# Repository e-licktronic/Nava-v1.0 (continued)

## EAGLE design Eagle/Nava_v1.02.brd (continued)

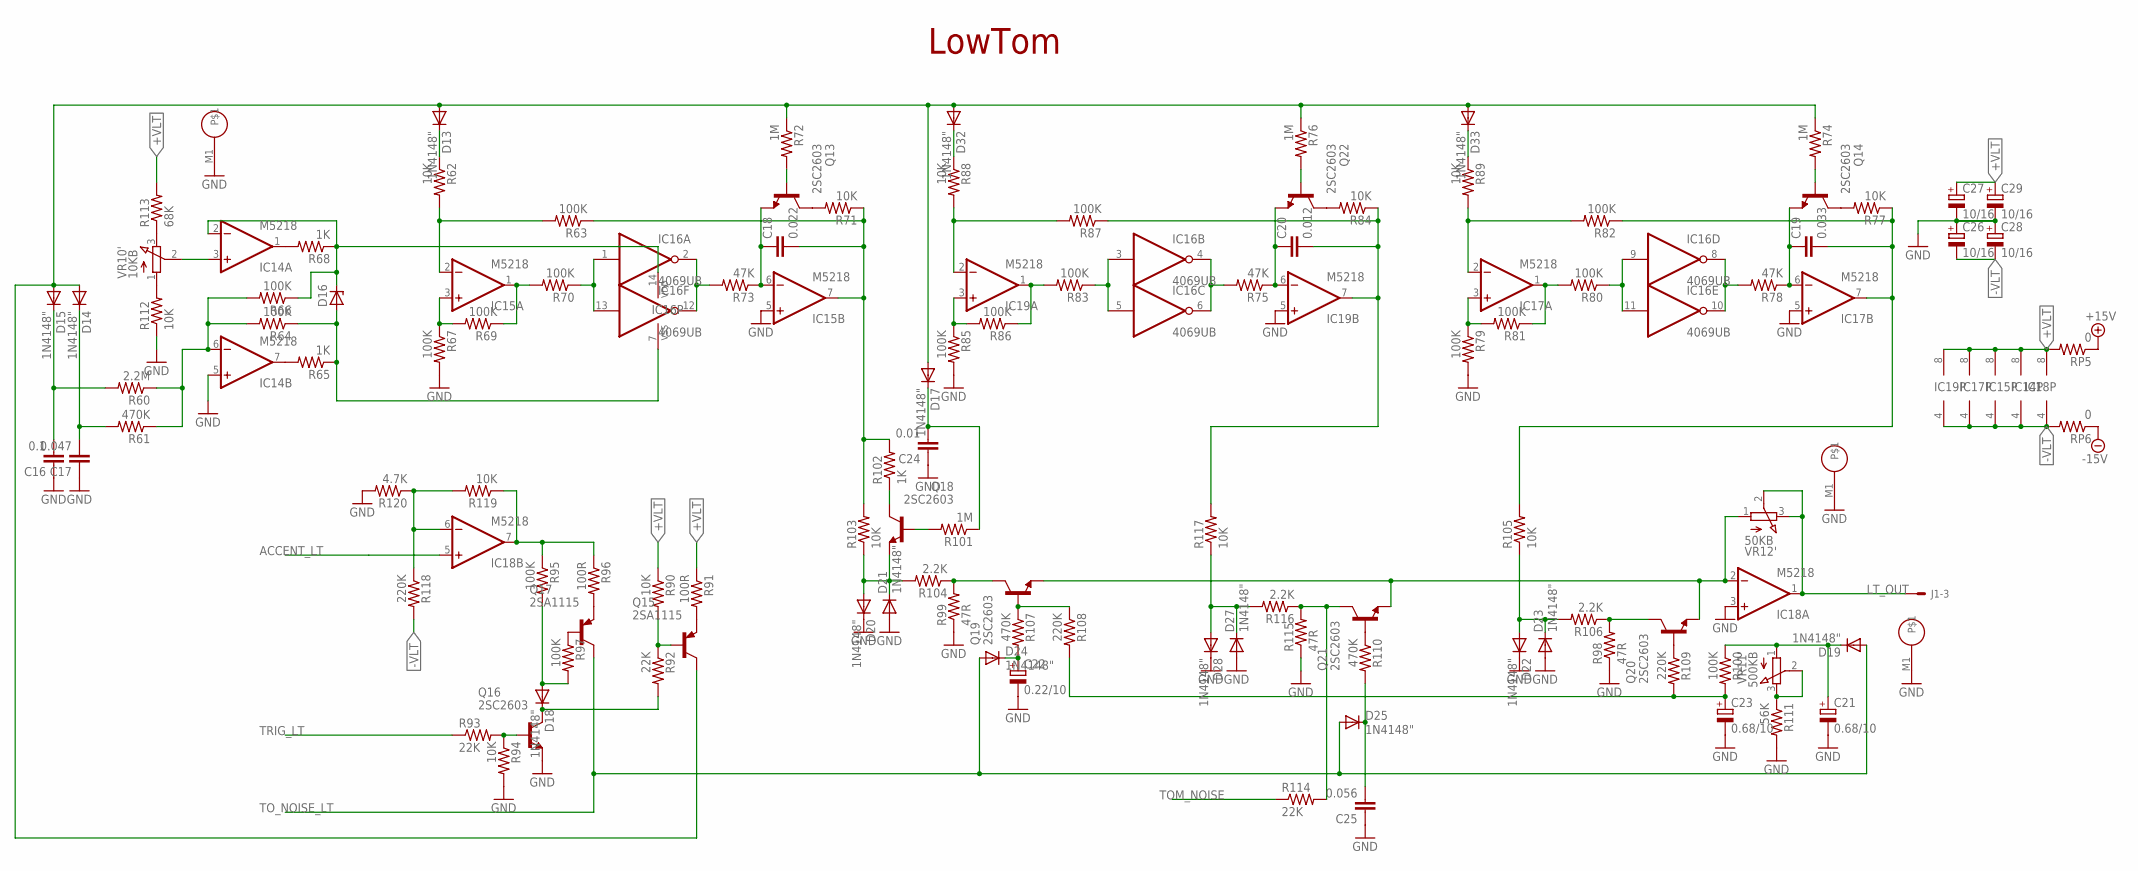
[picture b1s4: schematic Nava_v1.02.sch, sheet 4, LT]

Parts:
C16: 0.1; C050-025X075
C17: 0.047; C050-025X075
C18: 0.022; C050-025X075
C19: 0.033; C050-025X075
C20: 0.012; C050-025X075
C21, C23: 0.68/10; E2-5
C22: 0.22/10; E2-5
C24: 0.01; C050-025X075
C25: 0.056; C050-025X075
C26, C27, C28, C29: 10/16; E2-5
D13, D14, D15, D17, D18, D19, D20, D21, D22, D23, D24, D25, D27, D28, D32, D33: 1N4148"; DO35-7C
D16: ZENER-DIODE; DO41-7
IC14, IC15, IC17, IC18, IC19: M5218; SIL8
IC16: 4069UB; DIL14
J1: 22-27-2041-04; 6410-04
Q13, Q14, Q16, Q18, Q19, Q20, Q21, Q22: 2SC2603; TO92-ECB
Q15, Q17: 2SA1115; TO92-ECB-PNP
R60: 2.2M; 0207/7
R61, R107, R110: 470K; 0207/7
R62, R71, R77, R84, R88, R89, R90, R94, R103, R105, R112, R117, R119: 10K; 0207/7
R63, R64, R66, R67, R69, R70, R79, R80, R81, R82, R83, R85, R86, R87, R95, R97, R100: 100K; 0207/7
R65, R68, R102: 1K; 0207/7
R72, R74, R76, R101: 1M; 0207/7
R73, R75, R78: 47K; 0207/7
R91, R96: 100R; 0207/7
R92, R93, R114: 22K; 0207/7
R98, R99, R115: 47R; 0207/7
R104, R106, R116: 2.2K; 0207/7
R108, R109, R118: 220K; 0207/7
R111: 56K; 0207/7
R113: 68K; 0207/7
R120: 4.7K; 0207/7
RP5, RP6: 0; 0207/7
VR10: 10KB; EVUF
VR11: 500KB; EVUF
VR12: 50KB; EVUF

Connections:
+15V: RP5.1; also elsewhere on the board
+VLT: C27.+, C29.+, IC14.8 (V+), IC15.8 (V+), IC17.8 (V+), IC18.8 (V+), IC19.8 (V+), R90.1, R91.1, R113.2, RP5.2
-15V: RP6.1; also elsewhere on the board
-VLT: C26.-, C28.-, IC14.4 (V-), IC15.4 (V-), IC17.4 (V-), IC18.4 (V-), IC19.4 (V-), R118.2, RP6.2
ACCENT_LT: IC18.5 (+IN); also elsewhere on the board
GND: C16.1, C17.1, C21.-, C22.-, C23.-, C24.1, C25.1, C26.+, C27.-, C28.+, C29.-, D20.C, D21.A, D22.C, D23.A, D27.A, D28.C, IC14.5 (+IN), IC15.5 (+IN), IC17.5 (+IN), IC18.3 (+IN), IC19.5 (+IN), Q16.E, R67.2, R79.2, R85.2, R94.2, R98.1, R99.1, R111.2, R112.1, R115.1, R120.2, VR10.M1, VR11.M1, VR12.M1; also elsewhere on the board
LT_OUT: IC18.1 (OUT), J1.3, VR12.2 (S), VR12.3 (E)
unnamed: C18.1, IC15.6 (-IN), Q13.E, R73.1
unnamed: Q13.C, R71.2
unnamed: IC14.1 (OUT), R68.2
unnamed: IC14.7 (OUT), R65.2
unnamed: IC14.6 (-IN), R60.1, R61.1, R64.2, R66.2
unnamed: D16.A, IC16.7 (VSS), R64.1, R65.1
unnamed: D16.C, IC14.2 (-IN), IC16.14 (VDD), R66.1, R68.1
unnamed: R113.1, VR10.3 (E)
unnamed: R112.2, VR10.1 (A)
unnamed: IC14.3 (+IN), VR10.2 (S)
unnamed: IC15.3 (+IN), R67.1, R69.2
unnamed: IC15.2 (-IN), R62.2, R63.2
unnamed: IC15.1 (OUT), R69.1, R70.2
unnamed: IC16.1 (I), IC16.13 (I), R70.1
unnamed: IC16.2 (O), IC16.12 (O), R73.2
unnamed: Q13.B, R72.2
unnamed: C18.2, IC15.7 (OUT), R63.1, R71.1, R102.2, R103.2
unnamed: D13.C, R62.1
unnamed: C20.1, IC19.6 (-IN), Q22.E, R75.1
unnamed: Q22.C, R84.2
unnamed: IC19.3 (+IN), R85.1, R86.2
unnamed: IC19.2 (-IN), R87.2, R88.2
unnamed: IC19.1 (OUT), R83.2, R86.1
unnamed: IC16.3 (I), IC16.5 (I), R83.1
unnamed: IC16.4 (O), IC16.6 (O), R75.2
unnamed: Q22.B, R76.2
unnamed: C20.2, IC19.7 (OUT), R84.1, R87.1, R117.2
unnamed: D32.C, R88.1
unnamed: C19.1, IC17.6 (-IN), Q14.E, R78.1
unnamed: Q14.C, R77.2
unnamed: IC17.3 (+IN), R79.1, R81.2
unnamed: IC17.2 (-IN), R82.2, R89.2
unnamed: IC17.1 (OUT), R80.2, R81.1
unnamed: IC16.9 (I), IC16.11 (I), R80.1
unnamed: IC16.8 (O), IC16.10 (O), R78.2
unnamed: Q14.B, R74.2
unnamed: C19.2, IC17.7 (OUT), R77.1, R82.1, R105.2
unnamed: D33.C, R89.1
unnamed: C21.+, D19.C, R100.1, VR11.1 (A)
unnamed: C17.2, D14.C, R61.2
unnamed: C16.2, D15.C, R60.2
unnamed: D13.A, D14.A, D15.A, D17.A, D32.A, D33.A, Q15.C, R72.1, R74.1, R76.1
unnamed: Q19.B, R107.1, R108.1
unnamed: Q19.C, R99.2, R104.1
unnamed: D20.A, D21.C, Q18.E, R103.1, R104.2
unnamed: Q21.B, R110.1
unnamed: Q21.C, R114.2, R115.2, R116.1
unnamed: D27.C, D28.A, R116.2, R117.1
unnamed: Q20.B, R109.1
unnamed: Q20.C, R98.2, R106.1
unnamed: D22.A, D23.C, R105.1, R106.2
unnamed: Q18.C, R102.1
unnamed: C24.2, D17.C, R101.1
unnamed: Q18.B, R101.2
unnamed: R111.1, VR11.2 (S), VR11.3 (E)
unnamed: IC18.2 (-IN), Q19.E, Q20.E, Q21.E, VR12.1 (A)
unnamed: C23.+, R100.2, R108.2, R109.2
unnamed: C25.2, D25.C, R110.2
unnamed: C22.+, D24.C, R107.2
unnamed: Q17.E, R96.2
unnamed: Q17.B, R97.1
unnamed: D18.C, Q16.C, R92.2
unnamed: IC18.6 (-IN), R118.1, R119.2, R120.1
unnamed: IC18.7 (OUT), R95.1, R96.1, R119.1
unnamed: D18.A, R95.2, R97.2
unnamed: Q16.B, R93.2, R94.1
unnamed: Q15.E, R91.2
unnamed: Q15.B, R90.2, R92.1
TOM_NOISE: R114.1; also elsewhere on the board
TO_NOISE_LT: D19.A, D24.A, D25.A, Q17.C; also elsewhere on the board
TRIG_LT: R93.1; also elsewhere on the board

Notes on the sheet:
LowTom

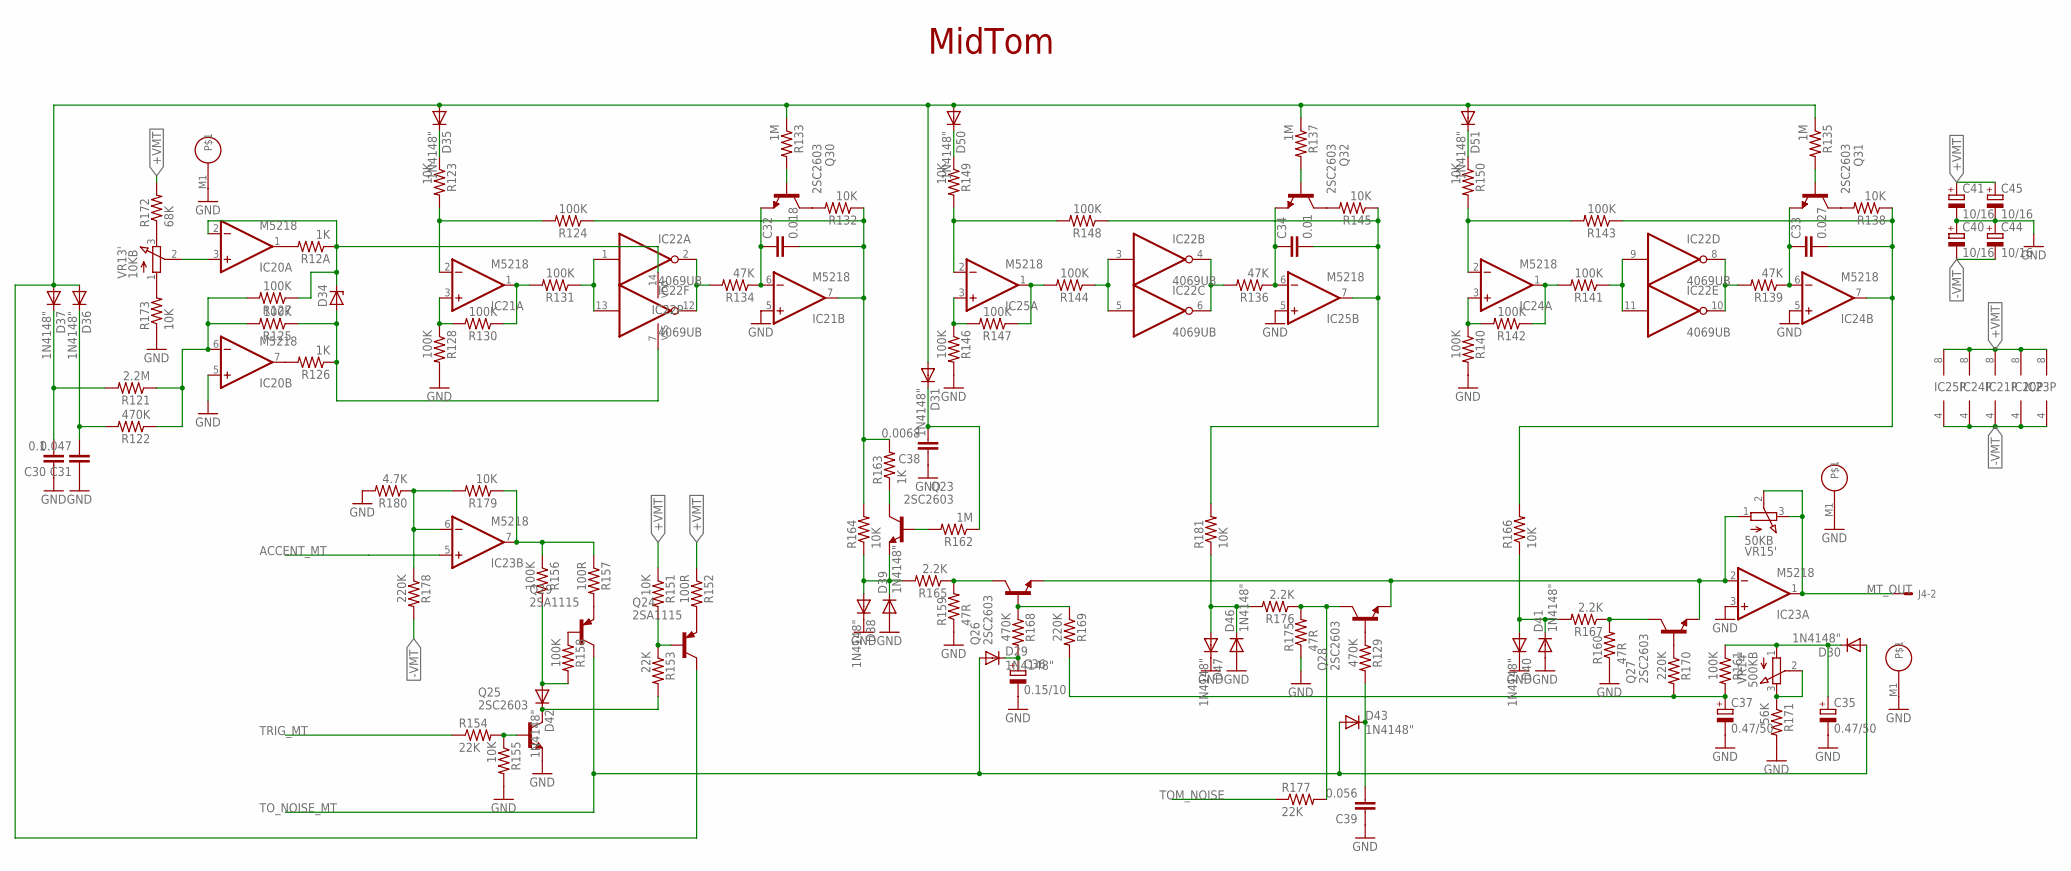
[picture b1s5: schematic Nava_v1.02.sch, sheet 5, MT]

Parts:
C30: 0.1; C050-025X075
C31: 0.047; C050-025X075
C32: 0.018; C050-025X075
C33: 0.027; C050-025X075
C34: 0.01; C050-025X075
C35, C37: 0.47/50; E2-5
C36: 0.15/10; E2-5
C38: 0.0068; C050-025X075
C39: 0.056; C050-025X075
C40, C41, C44, C45: 10/16; E2-5
D29, D30, D31, D35, D36, D37, D38, D39, D40, D41, D42, D43, D46, D47, D50, D51: 1N4148"; DO35-7C
D34: ZENER-DIODE; DO41-7
IC20, IC21, IC23, IC24, IC25: M5218; SIL8
IC22: 4069UB; DIL14
J4: 22-27-2041-04; 6410-04
Q23, Q25, Q26, Q27, Q28, Q30, Q31, Q32: 2SC2603; TO92-ECB
Q24, Q29: 2SA1115; TO92-ECB-PNP
R12A, R126, R163: 1K; 0207/7
R121: 2.2M; 0207/7
R122, R129, R168: 470K; 0207/7
R123, R132, R138, R145, R149, R150, R151, R155, R164, R166, R173, R179, R181: 10K; 0207/7
R124, R125, R127, R128, R130, R131, R140, R141, R142, R143, R144, R146, R147, R148, R156, R158, R161: 100K; 0207/7
R133, R135, R137, R162: 1M; 0207/7
R134, R136, R139: 47K; 0207/7
R152, R157: 100R; 0207/7
R153, R154, R177: 22K; 0207/7
R159, R160, R175: 47R; 0207/7
R165, R167, R176: 2.2K; 0207/7
R169, R170, R178: 220K; 0207/7
R171: 56K; 0207/7
R172: 68K; 0207/7
R180: 4.7K; 0207/7
VR13: 10KB; EVUF
VR14: 500KB; EVUF
VR15: 50KB; EVUF

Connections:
+VMT: C41.+, C45.+, IC20.8 (V+), IC21.8 (V+), IC23.8 (V+), IC24.8 (V+), IC25.8 (V+), R151.1, R152.1, R172.2; also elsewhere on the board
-VMT: C40.-, C44.-, IC20.4 (V-), IC21.4 (V-), IC23.4 (V-), IC24.4 (V-), IC25.4 (V-), R178.2; also elsewhere on the board
ACCENT_MT: IC23.5 (+IN); also elsewhere on the board
GND: C30.1, C31.1, C35.-, C36.-, C37.-, C38.1, C39.1, C40.+, C41.-, C44.+, C45.-, D38.C, D39.A, D40.C, D41.A, D46.A, D47.C, IC20.5 (+IN), IC21.5 (+IN), IC23.3 (+IN), IC24.5 (+IN), IC25.5 (+IN), Q25.E, R128.2, R140.2, R146.2, R155.2, R159.1, R160.1, R171.2, R173.1, R175.1, R180.2, VR13.M1, VR14.M1, VR15.M1; also elsewhere on the board
MT_OUT: IC23.1 (OUT), J4.2, VR15.2 (S), VR15.3 (E)
unnamed: C32.1, IC21.6 (-IN), Q30.E, R134.1
unnamed: Q30.C, R132.2
unnamed: IC20.1 (OUT), R12A.2
unnamed: IC20.7 (OUT), R126.2
unnamed: IC20.6 (-IN), R121.1, R122.1, R125.2, R127.2
unnamed: D34.A, IC22.7 (VSS), R125.1, R126.1
unnamed: D34.C, IC20.2 (-IN), IC22.14 (VDD), R12A.1, R127.1
unnamed: R172.1, VR13.3 (E)
unnamed: R173.2, VR13.1 (A)
unnamed: IC20.3 (+IN), VR13.2 (S)
unnamed: IC21.3 (+IN), R128.1, R130.2
unnamed: IC21.2 (-IN), R123.2, R124.2
unnamed: IC21.1 (OUT), R130.1, R131.2
unnamed: IC22.1 (I), IC22.13 (I), R131.1
unnamed: IC22.2 (O), IC22.12 (O), R134.2
unnamed: Q30.B, R133.2
unnamed: C32.2, IC21.7 (OUT), R124.1, R132.1, R163.2, R164.2
unnamed: D35.C, R123.1
unnamed: C34.1, IC25.6 (-IN), Q32.E, R136.1
unnamed: Q32.C, R145.2
unnamed: IC25.3 (+IN), R146.1, R147.2
unnamed: IC25.2 (-IN), R148.2, R149.2
unnamed: IC25.1 (OUT), R144.2, R147.1
unnamed: IC22.3 (I), IC22.5 (I), R144.1
unnamed: IC22.4 (O), IC22.6 (O), R136.2
unnamed: Q32.B, R137.2
unnamed: C34.2, IC25.7 (OUT), R145.1, R148.1, R181.2
unnamed: D50.C, R149.1
unnamed: C33.1, IC24.6 (-IN), Q31.E, R139.1
unnamed: Q31.C, R138.2
unnamed: IC24.3 (+IN), R140.1, R142.2
unnamed: IC24.2 (-IN), R143.2, R150.2
unnamed: IC24.1 (OUT), R141.2, R142.1
unnamed: IC22.9 (I), IC22.11 (I), R141.1
unnamed: IC22.8 (O), IC22.10 (O), R139.2
unnamed: Q31.B, R135.2
unnamed: C33.2, IC24.7 (OUT), R138.1, R143.1, R166.2
unnamed: D51.C, R150.1
unnamed: C31.2, D36.C, R122.2
unnamed: C30.2, D37.C, R121.2
unnamed: D31.A, D35.A, D36.A, D37.A, D50.A, D51.A, Q24.C, R133.1, R135.1, R137.1
unnamed: Q26.B, R168.1, R169.1
unnamed: Q26.C, R159.2, R165.1
unnamed: D38.A, D39.C, Q23.E, R164.1, R165.2
unnamed: Q28.B, R129.1
unnamed: Q28.C, R175.2, R176.1, R177.2
unnamed: D46.C, D47.A, R176.2, R181.1
unnamed: Q27.B, R170.1
unnamed: Q27.C, R160.2, R167.1
unnamed: D40.A, D41.C, R166.1, R167.2
unnamed: Q23.C, R163.1
unnamed: C38.2, D31.C, R162.1
unnamed: Q23.B, R162.2
unnamed: IC23.2 (-IN), Q26.E, Q27.E, Q28.E, VR15.1 (A)
unnamed: C35.+, D30.C, R161.1, VR14.1 (A)
unnamed: R171.1, VR14.2 (S), VR14.3 (E)
unnamed: C37.+, R161.2, R169.2, R170.2
unnamed: C39.2, D43.C, R129.2
unnamed: C36.+, D29.C, R168.2
unnamed: Q29.E, R157.2
unnamed: Q29.B, R158.1
unnamed: D42.C, Q25.C, R153.2
unnamed: IC23.6 (-IN), R178.1, R179.2, R180.1
unnamed: IC23.7 (OUT), R156.1, R157.1, R179.1
unnamed: D42.A, R156.2, R158.2
unnamed: Q25.B, R154.2, R155.1
unnamed: Q24.E, R152.2
unnamed: Q24.B, R151.2, R153.1
TOM_NOISE: R177.1; also elsewhere on the board
TO_NOISE_MT: D29.A, D30.A, D43.A, Q29.C; also elsewhere on the board
TRIG_MT: R154.1; also elsewhere on the board

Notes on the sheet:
MidTom

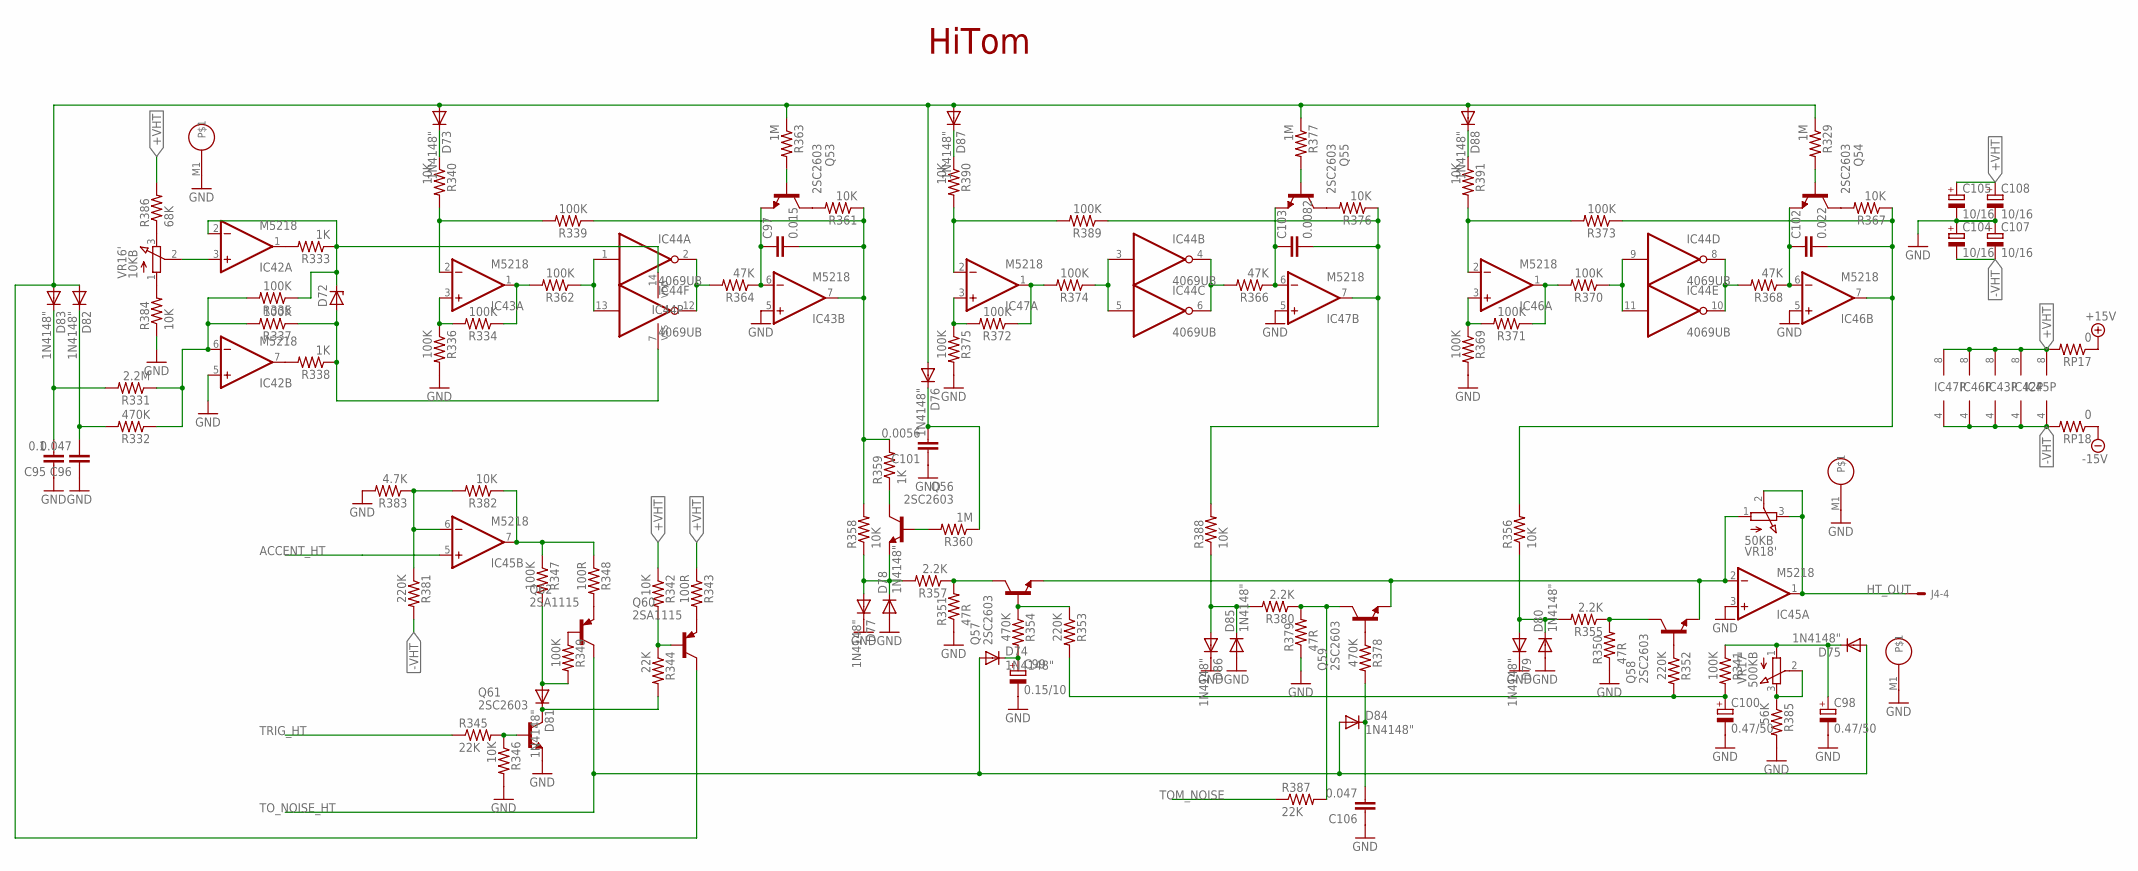
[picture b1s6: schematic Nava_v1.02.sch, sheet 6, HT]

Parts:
C95: 0.1; C050-025X075
C96, C106: 0.047; C050-025X075
C97: 0.015; C050-025X075
C98, C100: 0.47/50; E2-5
C99: 0.15/10; E2-5
C101: 0.0056; C050-025X075
C102: 0.022; C050-025X075
C103: 0.0082; C050-025X075
C104, C105, C107, C108: 10/16; E2-5
D72: ZENER-DIODE; DO41-7
D73, D74, D75, D76, D77, D78, D79, D80, D81, D82, D83, D84, D85, D86, D87, D88: 1N4148"; DO35-7C
IC42, IC43, IC45, IC46, IC47: M5218; SIL8
IC44: 4069UB; DIL14
J4: 22-27-2041-04; 6410-04
Q53, Q54, Q55, Q56, Q57, Q58, Q59, Q61: 2SC2603; TO92-ECB
Q60, Q62: 2SA1115; TO92-ECB-PNP
R329, R360, R363, R377: 1M; 0207/7
R331: 2.2M; 0207/7
R332, R354, R378: 470K; 0207/7
R333, R338, R359: 1K; 0207/7
R334, R335, R336, R337, R339, R341, R347, R349, R362, R369, R370, R371, R372, R373, R374, R375, R389: 100K; 0207/7
R340, R342, R346, R356, R358, R361, R367, R376, R382, R384, R388, R390, R391: 10K; 0207/7
R343, R348: 100R; 0207/7
R344, R345, R387: 22K; 0207/7
R350, R351, R379: 47R; 0207/7
R352, R353, R381: 220K; 0207/7
R355, R357, R380: 2.2K; 0207/7
R364, R366, R368: 47K; 0207/7
R383: 4.7K; 0207/7
R385: 56K; 0207/7
R386: 68K; 0207/7
RP17, RP18: 0; 0207/7
VR16: 10KB; EVUF
VR17: 500KB; EVUF
VR18: 50KB; EVUF

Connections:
+15V: RP17.1; also elsewhere on the board
+VHT: C105.+, C108.+, IC42.8 (V+), IC43.8 (V+), IC45.8 (V+), IC46.8 (V+), IC47.8 (V+), R342.1, R343.1, R386.2, RP17.2
-15V: RP18.1; also elsewhere on the board
-VHT: C104.-, C107.-, IC42.4 (V-), IC43.4 (V-), IC45.4 (V-), IC46.4 (V-), IC47.4 (V-), R381.2, RP18.2
ACCENT_HT: IC45.5 (+IN); also elsewhere on the board
GND: C95.1, C96.1, C98.-, C99.-, C100.-, C101.1, C104.+, C105.-, C106.1, C107.+, C108.-, D77.C, D78.A, D79.C, D80.A, D85.A, D86.C, IC42.5 (+IN), IC43.5 (+IN), IC45.3 (+IN), IC46.5 (+IN), IC47.5 (+IN), Q61.E, R336.2, R346.2, R350.1, R351.1, R369.2, R375.2, R379.1, R383.2, R384.1, R385.2, VR16.M1, VR17.M1, VR18.M1; also elsewhere on the board
HT_OUT: IC45.1 (OUT), J4.4, VR18.2 (S), VR18.3 (E)
unnamed: C97.1, IC43.6 (-IN), Q53.E, R364.1
unnamed: Q53.C, R361.2
unnamed: IC42.1 (OUT), R333.2
unnamed: IC42.7 (OUT), R338.2
unnamed: IC42.6 (-IN), R331.1, R332.1, R335.2, R337.2
unnamed: D72.A, IC44.7 (VSS), R337.1, R338.1
unnamed: D72.C, IC42.2 (-IN), IC44.14 (VDD), R333.1, R335.1
unnamed: R386.1, VR16.3 (E)
unnamed: R384.2, VR16.1 (A)
unnamed: IC42.3 (+IN), VR16.2 (S)
unnamed: IC43.3 (+IN), R334.2, R336.1
unnamed: IC43.2 (-IN), R339.2, R340.2
unnamed: IC43.1 (OUT), R334.1, R362.2
unnamed: IC44.1 (I), IC44.13 (I), R362.1
unnamed: IC44.2 (O), IC44.12 (O), R364.2
unnamed: Q53.B, R363.2
unnamed: C97.2, IC43.7 (OUT), R339.1, R358.2, R359.2, R361.1
unnamed: D73.C, R340.1
unnamed: C103.1, IC47.6 (-IN), Q55.E, R366.1
unnamed: Q55.C, R376.2
unnamed: IC47.3 (+IN), R372.2, R375.1
unnamed: IC47.2 (-IN), R389.2, R390.2
unnamed: IC47.1 (OUT), R372.1, R374.2
unnamed: IC44.3 (I), IC44.5 (I), R374.1
unnamed: IC44.4 (O), IC44.6 (O), R366.2
unnamed: Q55.B, R377.2
unnamed: C103.2, IC47.7 (OUT), R376.1, R388.2, R389.1
unnamed: D87.C, R390.1
unnamed: C102.1, IC46.6 (-IN), Q54.E, R368.1
unnamed: Q54.C, R367.2
unnamed: IC46.3 (+IN), R369.1, R371.2
unnamed: IC46.2 (-IN), R373.2, R391.2
unnamed: IC46.1 (OUT), R370.2, R371.1
unnamed: IC44.9 (I), IC44.11 (I), R370.1
unnamed: IC44.8 (O), IC44.10 (O), R368.2
unnamed: Q54.B, R329.2
unnamed: C102.2, IC46.7 (OUT), R356.2, R367.1, R373.1
unnamed: D88.C, R391.1
unnamed: C96.2, D82.C, R332.2
unnamed: C95.2, D83.C, R331.2
unnamed: D73.A, D76.A, D82.A, D83.A, D87.A, D88.A, Q60.C, R329.1, R363.1, R377.1
unnamed: Q57.B, R353.1, R354.1
unnamed: Q57.C, R351.2, R357.1
unnamed: D77.A, D78.C, Q56.E, R357.2, R358.1
unnamed: Q59.B, R378.1
unnamed: Q59.C, R379.2, R380.1, R387.2
unnamed: D85.C, D86.A, R380.2, R388.1
unnamed: Q58.B, R352.1
unnamed: Q58.C, R350.2, R355.1
unnamed: D79.A, D80.C, R355.2, R356.1
unnamed: Q56.C, R359.1
unnamed: C101.2, D76.C, R360.1
unnamed: Q56.B, R360.2
unnamed: IC45.2 (-IN), Q57.E, Q58.E, Q59.E, VR18.1 (A)
unnamed: C98.+, D75.C, R341.1, VR17.1 (A)
unnamed: R385.1, VR17.2 (S), VR17.3 (E)
unnamed: C100.+, R341.2, R352.2, R353.2
unnamed: C106.2, D84.C, R378.2
unnamed: C99.+, D74.C, R354.2
unnamed: Q62.E, R348.2
unnamed: Q62.B, R349.1
unnamed: D81.C, Q61.C, R344.2
unnamed: IC45.6 (-IN), R381.1, R382.2, R383.1
unnamed: IC45.7 (OUT), R347.1, R348.1, R382.1
unnamed: D81.A, R347.2, R349.2
unnamed: Q61.B, R345.2, R346.1
unnamed: Q60.E, R343.2
unnamed: Q60.B, R342.2, R344.1
TOM_NOISE: R387.1; also elsewhere on the board
TO_NOISE_HT: D74.A, D75.A, D84.A, Q62.C; also elsewhere on the board
TRIG_HT: R345.1; also elsewhere on the board

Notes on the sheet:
HiTom

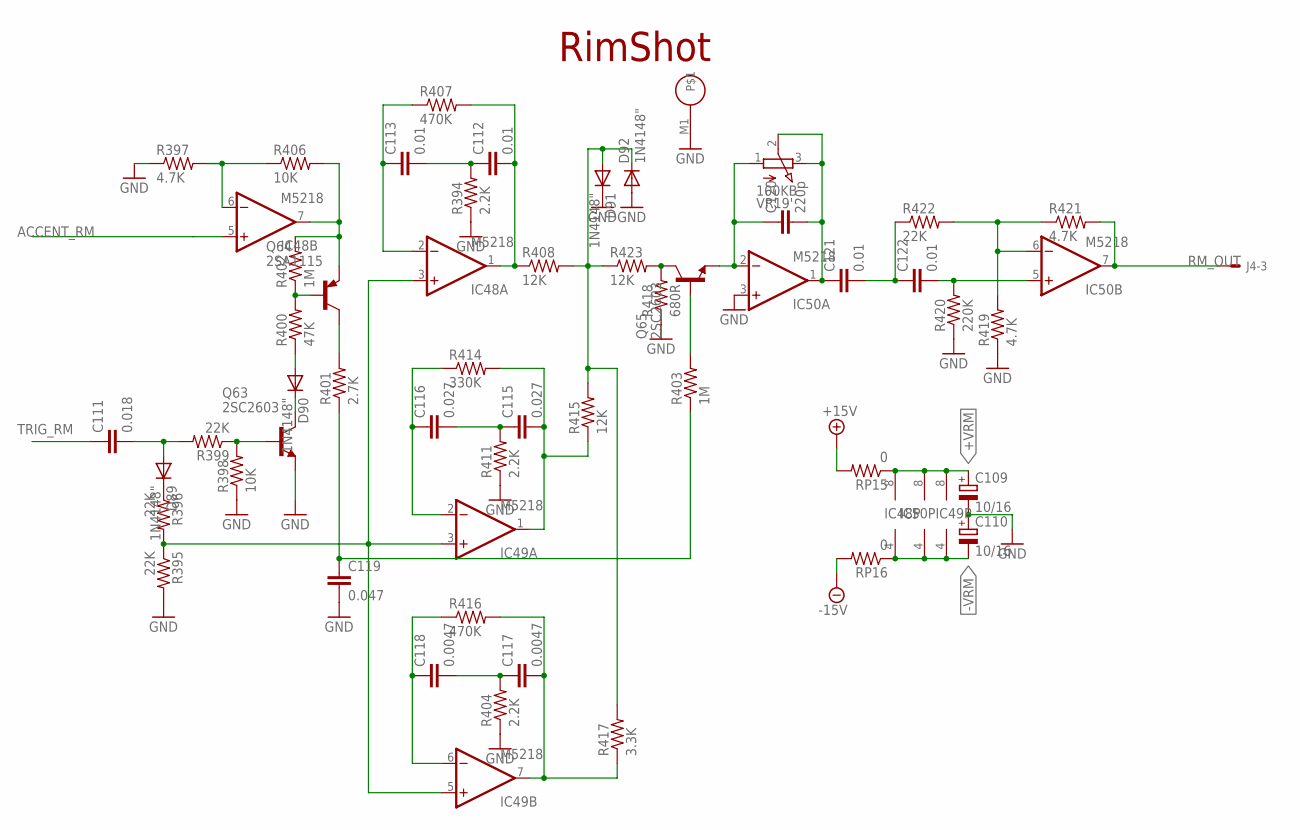
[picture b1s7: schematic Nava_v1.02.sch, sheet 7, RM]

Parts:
C109, C110: 10/16; E2-5
C111: 0.018; C050-025X075
C112, C113, C121, C122: 0.01; C050-025X075
C115, C116: 0.027; C050-025X075
C117, C118: 0.0047; C050-025X075
C119: 0.047; C050-025X075
C120: 220p; C050-025X075
D89, D90, D91, D92: 1N4148"; DO35-7C
IC48, IC49, IC50: M5218; SIL8
J4: 22-27-2041-04; 6410-04
Q63, Q65: 2SC2603; TO92-ECB
Q64: 2SA1115; TO92-ECB-PNP
R394, R404, R411: 2.2K; 0207/7
R395, R396, R399, R422: 22K; 0207/7
R397, R419, R421: 4.7K; 0207/7
R398, R406: 10K; 0207/7
R400: 47K; 0207/7
R401: 2.7K; 0207/7
R402, R403: 1M; 0207/7
R407, R416: 470K; 0207/7
R408, R415, R423: 12K; 0207/7
R414: 330K; 0207/7
R417: 3.3K; 0207/7
R418: 680R; 0207/7
R420: 220K; 0207/7
RP15, RP16: 0; 0207/7
VR19: 100KB; EVUF

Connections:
+15V: RP15.2; also elsewhere on the board
+VRM: C109.+, IC48.8 (V+), IC49.8 (V+), IC50.8 (V+), RP15.1
-15V: RP16.2; also elsewhere on the board
-VRM: C110.-, IC48.4 (V-), IC49.4 (V-), IC50.4 (V-), RP16.1
ACCENT_RM: IC48.5 (+IN); also elsewhere on the board
C117: C117.2, IC49.7 (OUT), R416.2, R417.1
GND: C109.-, C110.+, C119.2, D91.C, D92.A, IC50.3 (+IN), Q63.E, R394.1, R395.2, R397.1, R398.1, R404.1, R411.1, R418.1, R419.1, R420.1, VR19.M1; also elsewhere on the board
unnamed: C115.1, C116.2, R411.2
unnamed: C116.1, IC49.2 (-IN), R414.1
unnamed: C115.2, IC49.1 (OUT), R414.2, R415.1
unnamed: C112.1, C113.2, R394.2
unnamed: C113.1, IC48.2 (-IN), R407.1
unnamed: C112.2, IC48.1 (OUT), R407.2, R408.1
unnamed: C117.1, C118.2, R404.2
unnamed: C118.1, IC49.6 (-IN), R416.1
unnamed: Q64.B, R400.2, R402.1
unnamed: Q63.B, R398.2, R399.1
unnamed: D89.C, R396.1
unnamed: IC48.3 (+IN), IC49.3 (+IN), IC49.5 (+IN), R395.1, R396.2
unnamed: C111.2, D89.A, R399.2
unnamed: D90.C, Q63.C
unnamed: D90.A, R400.1
unnamed: Q64.C, R401.2
unnamed: C119.1, R401.1, R403.1
unnamed: IC48.7 (OUT), Q64.E, R402.2, R406.2
unnamed: IC48.6 (-IN), R397.2, R406.1
unnamed: Q65.C, R418.2, R423.2
unnamed: D91.A, D92.C, R408.2, R415.2, R417.2, R423.1
unnamed: Q65.B, R403.2
unnamed: C120.1, IC50.2 (-IN), Q65.E, VR19.1 (A)
unnamed: C120.2, C121.1, IC50.1 (OUT), VR19.2 (S), VR19.3 (E)
unnamed: C121.2, C122.1, R422.1
unnamed: IC50.6 (-IN), R419.2, R421.1, R422.2
unnamed: C122.2, IC50.5 (+IN), R420.2
RM_OUT: IC50.7 (OUT), J4.3, R421.2
TRIG_RM: C111.1; also elsewhere on the board

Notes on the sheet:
RimShot

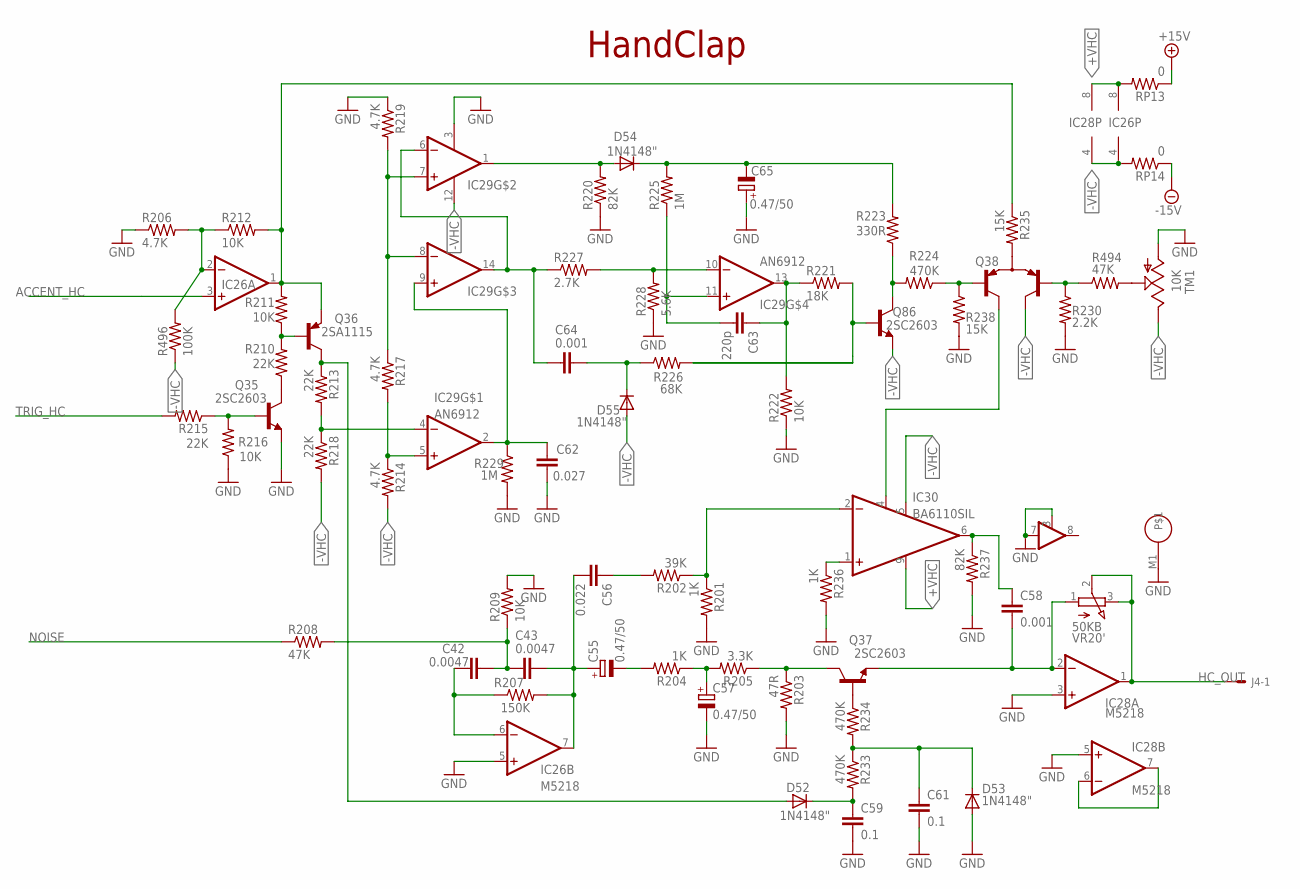
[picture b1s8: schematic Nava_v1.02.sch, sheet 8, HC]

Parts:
C42, C43: 0.0047; C050-025X075
C55, C57, C65: 0.47/50; E2-5
C56: 0.022; C050-025X075
C58, C64: 0.001; C050-025X075
C59, C61: 0.1; C050-025X075
C62: 0.027; C050-025X075
C63: 220p; C050-025X075
D52, D53, D54, D55: 1N4148"; DO35-7C
IC26, IC28: M5218; SIL8
IC29: AN6912; DIL14
IC30: BA6110SIL; SIL09
J4: 22-27-2041-04; 6410-04
Q35, Q37, Q86: 2SC2603; TO92-ECB
Q36: 2SA1115; TO92-ECB-PNP
Q38: 2SA798; SIP-5
R201, R204, R236: 1K; 0207/7
R202: 39K; 0207/7
R203: 47R; 0207/7
R205: 3.3K; 0207/7
R206, R214, R217, R219: 4.7K; 0207/7
R207: 150K; 0207/7
R208, R494: 47K; 0207/7
R209, R211, R212, R216, R222: 10K; 0207/7
R210, R213, R215, R218: 22K; 0207/7
R220, R237: 82K; 0207/7
R221: 18K; 0207/7
R223: 330R; 0207/7
R224, R233, R234: 470K; 0207/7
R225, R229: 1M; 0207/7
R226: 68K; 0207/7
R227: 2.7K; 0207/7
R228: 5.6K; 0207/7
R230: 2.2K; 0207/7
R235, R238: 15K; 0207/7
R496: 100K; 0207/7
RP13, RP14: 0; 0207/7
TM1: 10K; S64W
VR20: 50KB; EVUF

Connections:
+15V: RP13.1; also elsewhere on the board
+VHC: IC26.8 (V+), IC28.8 (V+), IC30.9 (V+), RP13.2
-15V: RP14.1; also elsewhere on the board
-VHC: D55.A, IC26.4 (V-), IC28.4 (V-), IC29.12 (V-), IC30.5 (V-), Q38.4 (C2), Q86.E, R214.2, R218.2, R496.1, RP14.2, TM1.E
ACCENT_HC: IC26.3 (+IN); also elsewhere on the board
GND: C57.-, C59.2, C61.2, C62.1, C65.+, D53.A, IC26.5 (+IN), IC28.3 (+IN), IC28.5 (+IN), IC29.3 (V+), IC30.3, IC30.7 (IN1), Q35.E, R201.2, R203.2, R206.1, R209.2, R216.1, R219.1, R220.1, R222.1, R228.1, R229.2, R230.2, R236.2, R237.2, R238.2, TM1.A, VR20.M1; also elsewhere on the board
HC_OUT: IC28.1 (OUT), J4.1, VR20.2 (S), VR20.3 (E)
unnamed: IC26.1 (OUT), Q36.E, R211.2, R212.2, R235.1
unnamed: IC26.2 (-IN), R206.2, R212.1, R496.2
unnamed: Q86.B, R221.2, R226.2
unnamed: C63.1, IC29.13 (OUT), R221.1, R222.2
unnamed: Q36.B, R210.2, R211.1
unnamed: Q35.C, R210.1
unnamed: D52.A, Q36.C, R213.1
unnamed: Q35.B, R215.1, R216.2
unnamed: C58.1, IC30.6 (OUT), R237.1
unnamed: IC29.4 (-IN), R213.2, R218.1
unnamed: IC29.5 (+IN), R214.1, R217.2
unnamed: IC29.7 (+IN), IC29.8 (-IN), R217.1, R219.2
unnamed: C64.2, IC29.6 (-IN), IC29.14 (OUT), R227.1
unnamed: C62.2, IC29.2 (OUT), IC29.9 (+IN), R229.1
unnamed: D54.A, IC29.1 (OUT), R220.2
unnamed: C65.-, D54.C, R223.2, R225.2
unnamed: C63.2, IC29.11 (+IN), R225.1
unnamed: IC29.10 (-IN), R227.2, R228.2
unnamed: C64.1, D55.C, R226.1
unnamed: Q86.C, R223.1, R224.2
unnamed: Q38.1 (B1), R224.1, R238.1
unnamed: R494.2, TM1.S
unnamed: Q37.B, R234.1
unnamed: C61.1, D53.C, R233.1, R234.2
unnamed: IC30.2 (-IN), R201.1, R202.1
unnamed: C56.1, R202.2
unnamed: C42.1, C43.2, R208.2, R209.1
unnamed: C42.2, IC26.6 (-IN), R207.1
unnamed: C43.1, C55.+, C56.2, IC26.7 (OUT), R207.2
unnamed: IC30.1 (+IN), R236.1
unnamed: C55.-, R204.2
unnamed: C57.+, R204.1, R205.2
unnamed: Q37.C, R203.1, R205.1
unnamed: C59.1, D52.C, R233.2
unnamed: C58.2, IC28.2 (-IN), Q37.E, VR20.1 (A)
unnamed: Q38.5 (B2), R230.1, R494.1
unnamed: Q38.3 (E), R235.2
unnamed: IC30.4 (C), Q38.2 (C1)
unnamed: IC28.6 (-IN), IC28.7 (OUT)
NOISE: R208.1; also elsewhere on the board
TRIG_HC: R215.2; also elsewhere on the board

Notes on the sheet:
HandClap

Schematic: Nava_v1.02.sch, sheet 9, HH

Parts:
C134: 0.01; C050-025X075
C135: 1/50; E2-5
C148: 0.0012; C050-025X075
C149, C156: 0.001; C050-025X075
C150: 0.0027; C050-025X075
C151: 390p; C025_RE
C157, C158: 10/16; E2-5
C159: 100p; C050-025X075
C160: 470p; C025_RE
D196, D197, D198, D199: 1N4148"; DO35-7C
IC65, IC67: M5218; SIL8
IC68: 74HC174; DIL16
IC69: 27C256P; DIL28-6
IC70: 4520N; DIL16
IC71: 4040N; DIL16
IC72: 4011UB; DIL14
IC73: 4013N; DIL14
J3: 22-27-2041-04; 6410-04
Q52, Q72, Q74, Q80, Q81: 2SC2603; TO92-ECB
Q73: 2SA1115; TO92-ECB-PNP
Q84: 2SA798; SIP-5
R444, R447, R449, R454: 22K; 0207/7
R448, R450, R451, R455, R476, R478, R485, R486, R487: 10K; 0207/7
R452, R491: 100K; 0207/7
R453: 220K; 0207/7
R475, R477, R479, R480: 5.6K; 0207/7
R481: 4.7K; 0207/7
R482: 22R; 0207/7
R483: 47K; 0207/7
R484, R488: 2.2K; 0207/7
R489: 150R; 0207/7
R490: 100R; 0207/7
R492: 12K; 0207/7
R493: 33K; 0207/7
RA9A: 5K; 0207/7
RA9B: 10K; 0207/7
RA9C: 20K; 0207/7
RA9D: 40K; 0207/7
RA9E: 80K; 0207/7
RA9F: 160K; 0207/7
RP9, RP10: 0; 0207/7
VR21: 100KB; EVUF
VR22: 50KB; EVUF
VR23: 1MA; EVUF

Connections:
+5V: C158.+, IC67.3 (+IN), IC68.1 (RES), IC68.16 (VDD), IC69.1 (VPP), IC69.28 (VCC), IC70.16 (VDD), IC71.16 (VDD), IC72.14 (VDD), IC73.14 (VDD), Q73.E, R450.2, R452.2, R489.2, R490.2; also elsewhere on the board
+15V: RP9.1; also elsewhere on the board
+VHH: IC67.8 (V+), Q80.C, Q81.C, RP9.2; also elsewhere on the board
-15V: RP10.1; also elsewhere on the board
-VHH: IC67.4 (V-), R476.2, R478.2, RP10.2; also elsewhere on the board
ACCENT_HH: R481.1; also elsewhere on the board
CRASH_OUT2: C135.+, Q74.C, R453.1, VR21.2 (S), VR21.3 (E), VR23.2 (S), VR23.3 (E)
GND: C135.-, C149.1, C151.- (2), C158.-, IC65.5 (+IN), IC67.5 (+IN), IC68.8 (VSS), IC69.14 (GND), IC70.1 (CLK), IC70.2 (EN), IC70.8 (VSS), IC70.9 (CLK), IC71.8 (VSS), IC72.7 (VSS), IC73.6 (S), IC73.7 (VSS), IC73.8 (S), Q72.E, Q74.E, R448.1, R455.1, R482.1, R486.1, R487.1, R491.2, VR21.M1, VR22.M1, VR23.M1; also elsewhere on the board
HH_OUT: IC65.7 (OUT), J3.3, VR22.2 (S), VR22.3 (E)
HT_OUT3: IC72.10 (O), IC72.12 (I0), IC73.3 (CLK), R492.1
unnamed: IC72.8 (I0), IC72.9 (I1), R493.2
unnamed: C160.+ (1), R492.2, R493.1
unnamed: IC72.3 (O), IC72.13 (I1), R488.1
unnamed: C160.- (2), IC72.11 (O), IC73.11 (CLK)
unnamed: IC73.2 (!Q), IC73.5 (D)
unnamed: IC71.10 (P1), IC72.5 (I0), IC73.13 (Q)
unnamed: IC72.6 (I1), IC73.1 (Q)
unnamed: IC68.9 (CLK), IC72.4 (O)
unnamed: D197.C, D199.C, IC69.26 (A13), R487.2
unnamed: C157.+, RA9A.2, RA9B.2, RA9C.2, RA9D.2, RA9E.2, RA9F.2
unnamed: D196.C, D198.C, IC69.27 (A14), IC72.1 (I0), R486.2
unnamed: Q52.B, R485.2
unnamed: Q84.2 (C1), R485.1
unnamed: Q84.1 (B1), R490.1
unnamed: C157.-, Q52.C, R482.2
unnamed: Q84.3 (E), R484.1
unnamed: Q84.5 (B2), R481.2, R488.2, R489.1
unnamed: C150.2, R477.1, R479.2
unnamed: C148.2, R475.2, R480.1
unnamed: C149.2, Q80.B, R475.1
unnamed: C151.+ (1), Q81.B, R479.1
unnamed: IC67.6 (-IN), Q52.E, R483.2
unnamed: IC67.7 (OUT), R480.2, R483.1
unnamed: C148.1, Q80.E, R476.1, R477.2
unnamed: C134.2, C150.1, Q81.E, R478.1
unnamed: IC65.6 (-IN), R444.1, VR22.1 (A)
unnamed: C134.1, R444.2
unnamed: IC69.23 (A11), IC70.10 (EN), IC71.1 (Q12)
unnamed: IC69.5 (A5), IC71.2 (Q6)
unnamed: IC69.6 (A4), IC71.3 (Q5)
unnamed: IC69.4 (A6), IC71.4 (Q7)
unnamed: IC69.7 (A3), IC71.5 (Q4)
unnamed: IC69.8 (A2), IC71.6 (Q3)
unnamed: IC69.9 (A1), IC71.7 (Q2)
unnamed: IC69.10 (A0), IC71.9 (Q1)
unnamed: IC69.25 (A8), IC71.12 (Q9)
unnamed: IC69.3 (A7), IC71.13 (Q8)
unnamed: IC69.24 (A9), IC71.14 (Q10)
unnamed: IC69.21 (A10), IC71.15 (Q11)
unnamed: IC69.2 (A12), IC70.11 (Q0)
unnamed: D199.A, IC70.12 (Q1), IC72.2 (I1)
unnamed: D198.A, IC70.13 (Q2)
unnamed: Q74.B, R454.1, R455.2
unnamed: IC68.3 (D0), IC69.19 (D7)
unnamed: IC68.4 (D1), IC69.18 (D6)
unnamed: IC68.6 (D2), IC69.17 (D5)
unnamed: IC68.11 (D3), IC69.16 (D4)
unnamed: IC68.13 (D4), IC69.15 (D3)
unnamed: IC68.14 (D5), IC69.13 (D2)
unnamed: IC68.2 (Q0), RA9A.1
unnamed: IC68.5 (Q1), RA9B.1
unnamed: IC68.7 (Q2), RA9C.1
unnamed: IC68.10 (Q3), RA9D.1
unnamed: IC68.12 (Q4), RA9E.1
unnamed: IC68.15 (Q5), RA9F.1
unnamed: C156.1, IC67.1 (OUT), R484.2
unnamed: C159.2, IC70.15 (RES), IC71.11 (RES), IC73.4 (R), IC73.10 (R), R491.1
unnamed: C156.2, IC67.2 (-IN), Q84.4 (C2), R453.2
unnamed: IC69.20 (!CE), IC69.22 (!OE), IC73.9 (D), IC73.12 (!Q)
unnamed: R452.1, VR23.1 (A)
unnamed: R451.1, VR21.1 (A)
unnamed: Q73.C, R451.2
unnamed: Q72.C, R449.1
unnamed: Q73.B, R449.2, R450.1
unnamed: Q72.B, R447.1, R448.2
SELECT_HH: D196.A, D197.A, R447.2; also elsewhere on the board
TRIG_HH: C159.1, R454.2; also elsewhere on the board

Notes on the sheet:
HitHat
0: Open HAT
1: Closed HAT
Polystyrene
